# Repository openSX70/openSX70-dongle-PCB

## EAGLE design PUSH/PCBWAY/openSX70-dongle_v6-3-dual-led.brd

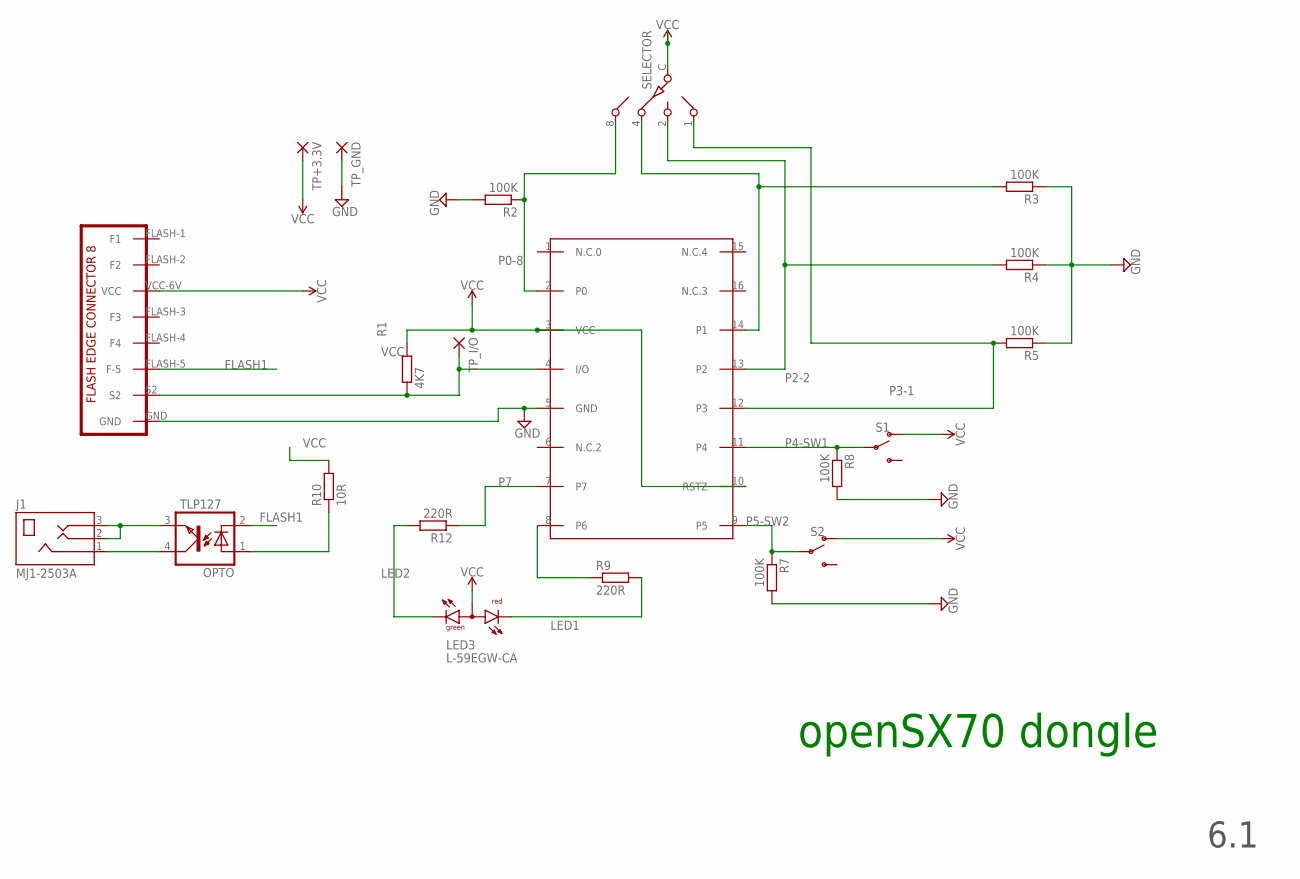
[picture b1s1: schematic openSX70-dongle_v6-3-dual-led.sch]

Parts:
DS2408: DS2408; SO16
J1: MJ1-2503A; CUI_MJ1-2503A
LED3: L-59EGW-CA
OPTO: TLP127; SO-4
R1: 4K7; R0603
R2, R3, R4, R5, R7, R8: 100K; R0603
R9, R12: 220R; R0603
R10: 10R; R0603
S1, S2: SWITCH-SPDT-SMD-RIGHT-ANGLE; SWITCH_SPST_SMD_A
SELECTOR: SW-C16
TP+3.3V: SMD2; SMD1,27-2,54
TP_GND: SMD2; SMD1,27-2,54
TP_I/O: SMD2; SMD1,27-2,54
U$2: SX70-FLASH-EDGE8-MALE-PROPER; SX70-FLASH-EDGE8

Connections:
FLASH1: OPTO.2 (C), U$2.FLASH-5 (F-5)
GND: DS2408.5 (GND), R2.2, R3.1, R4.1, R5.1, R7.2, R8.2, TP_GND.1, U$2.GND
LED1: LED3.1 (CR), R9.2
LED2: LED3.3 (CG), R12.2
unnamed: J1.1, OPTO.4 (COL)
unnamed: OPTO.1 (A), R10.1
unnamed: J1.2, J1.3, OPTO.3 (EMIT)
P0-8: DS2408.2 (P0), R2.1, SELECTOR.8
P1-4: DS2408.14 (P1), R3.2, SELECTOR.4
P2-2: DS2408.13 (P2), R4.2, SELECTOR.2
P3-1: DS2408.12 (P3), R5.2, SELECTOR.1
P4-SW1: DS2408.11 (P4), R8.1, S1.2
P5-SW2: DS2408.9 (P5), R7.1, S2.2
P6: DS2408.8 (P6), R9.1
P7: DS2408.7, R12.1
S2+: DS2408.4 (I/O), R1.1, TP_I/O.1, U$2.S2
VCC: DS2408.3 (VCC), DS2408.10 (RSTZ), LED3.2 (A), R1.2, R10.2, S1.1 (O), S2.1 (O), SELECTOR.C, TP+3.3V.1, U$2.VCC-6V (VCC)

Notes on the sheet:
openSX70 dongle
6.1

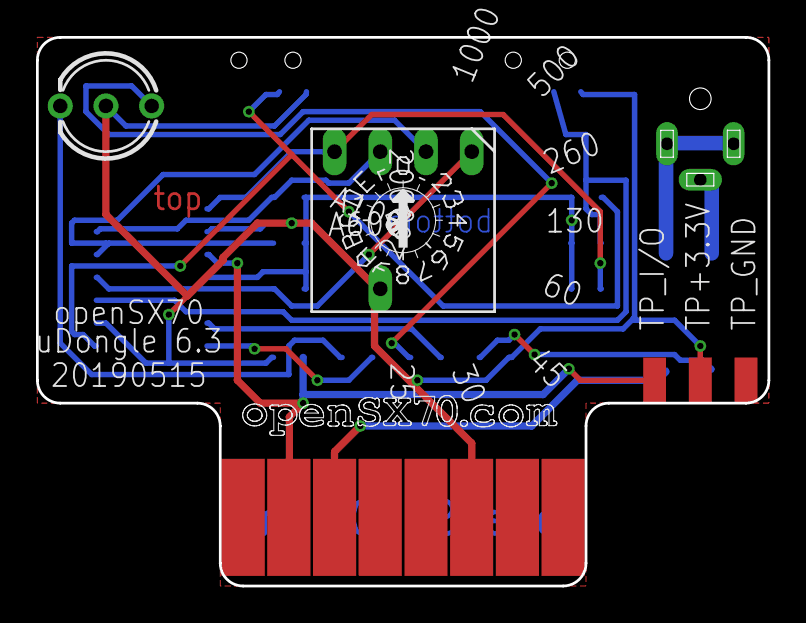
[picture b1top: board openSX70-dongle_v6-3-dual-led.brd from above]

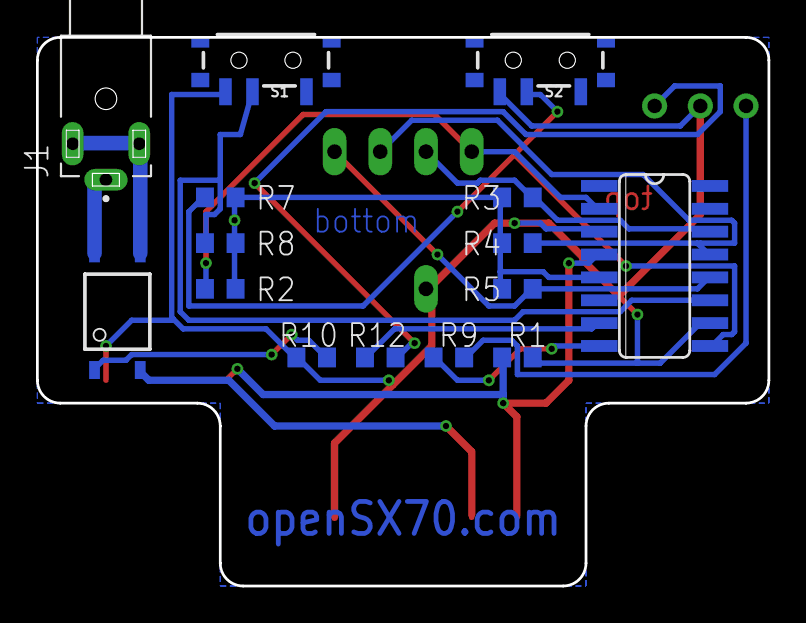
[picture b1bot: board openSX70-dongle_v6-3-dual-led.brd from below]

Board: 2 copper layers, 40.6 x 30.5 mm, 21 parts (15 on the bottom side), 17 nets.

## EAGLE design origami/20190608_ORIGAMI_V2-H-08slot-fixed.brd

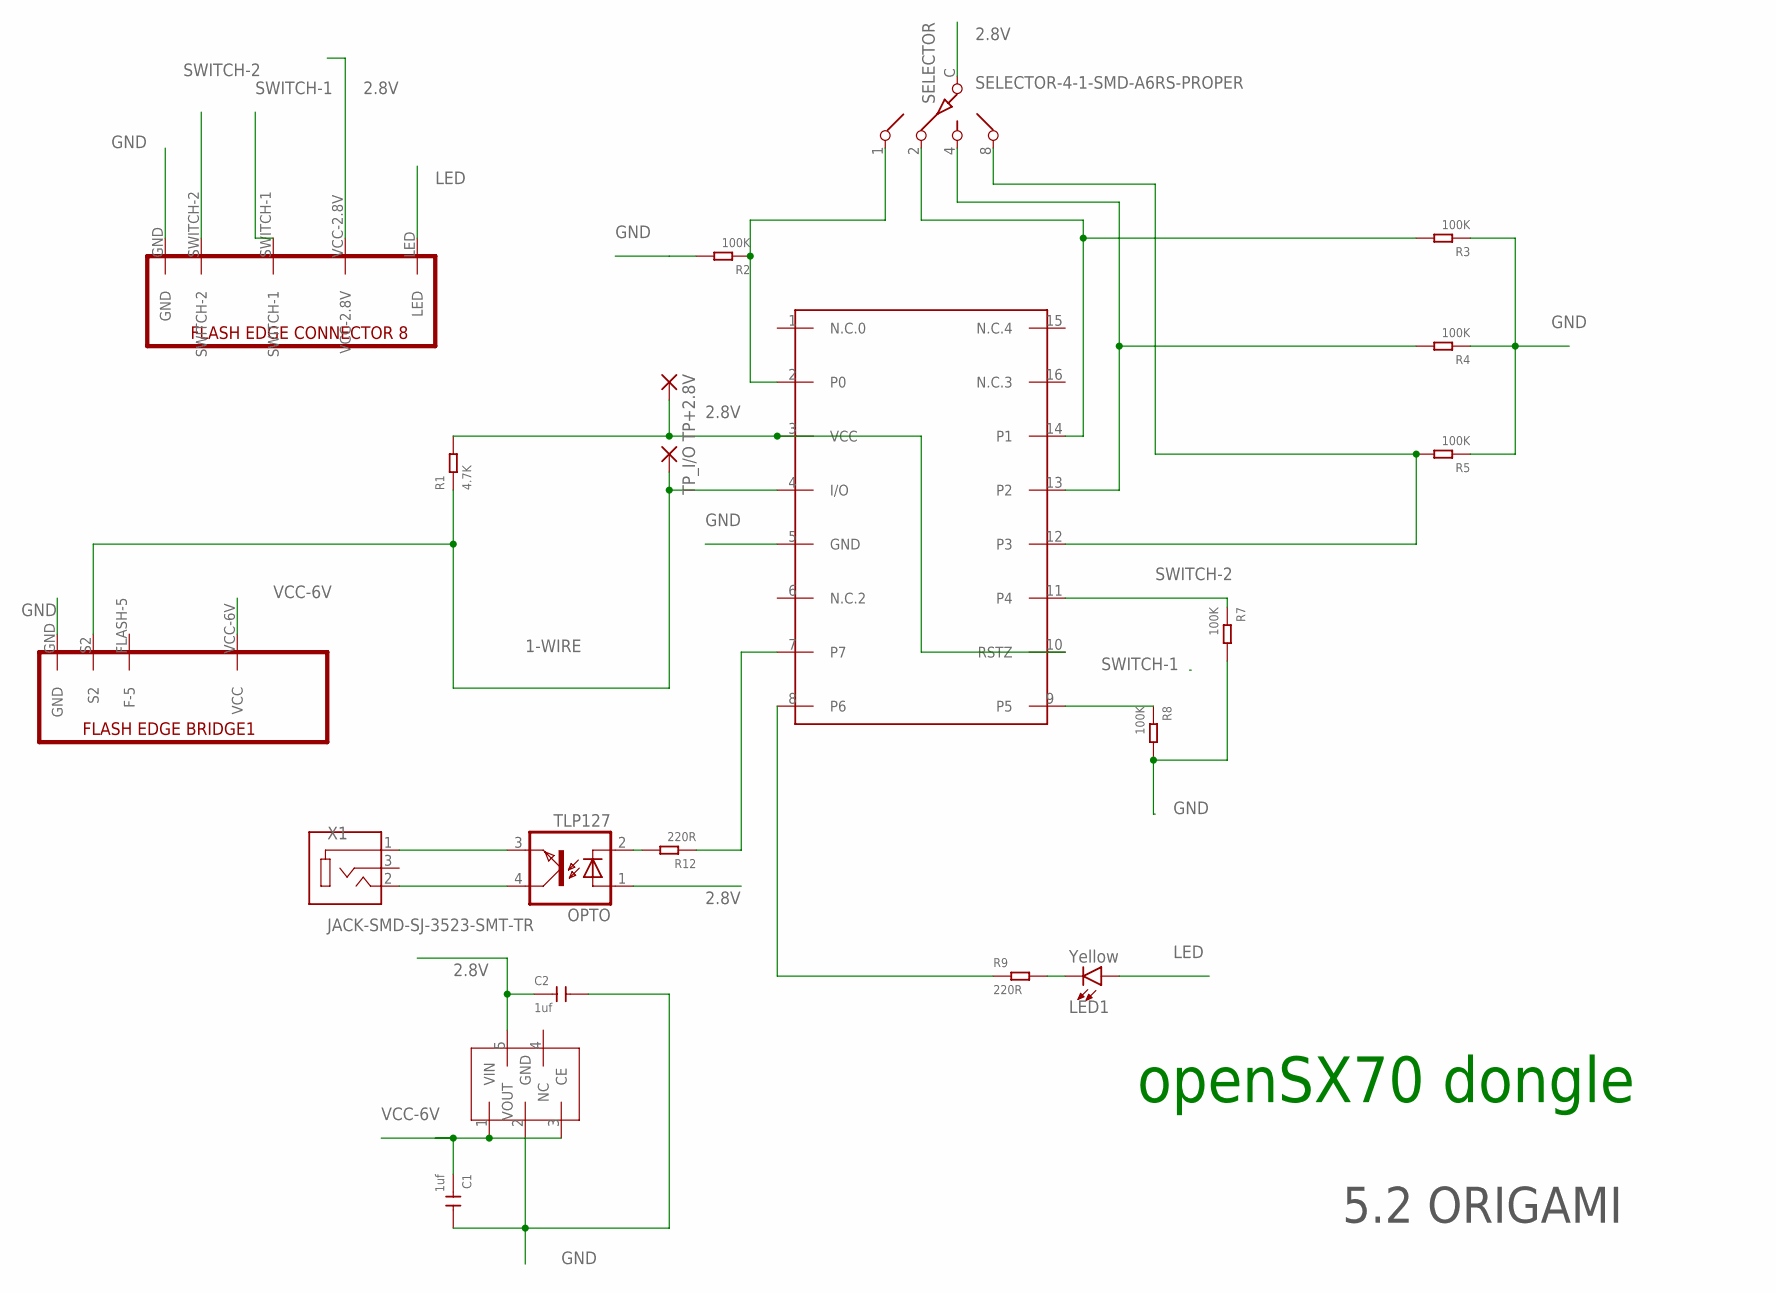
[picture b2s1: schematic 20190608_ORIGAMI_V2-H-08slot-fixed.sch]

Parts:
C1, C2: 1uf; C0603
DS2408: DS2408; SO16
LED1: Yellow; LED-1206
OPTO: TLP127; SO-4
R1: 4.7K; R0603
R2, R3, R4, R5, R7, R8: 100K; R0603
R9, R12: 220R; R0603
REG: NCP4688; SOT-23-5
SELECTOR: SELECTOR-4-1-SMD-A6RS-PROPER; A6RS-161RS
TP+2.8V: SMD2; SMD1,27-2,54
TP_I/O: SMD2; SMD1,27-2,54
U$1: FLASH-BRIDGE-SW1-SW2-LED; FLASH-8-BRIDGE-SW1-SW2-LED
U$2: FLASH-BRIDGE1; FLASH-8-BRIDGE1
X1: JACK-SMD-SJ-3523-SMT-TR; CUI_SJ-3523-SMT-TR

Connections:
1-WIRE: DS2408.4 (I/O), R1.1, TP_I/O.1, U$2.S2
2.8V: C2.1, DS2408.3 (VCC), DS2408.10 (RSTZ), OPTO.1 (A), R1.2, REG.5 (VOUT), SELECTOR.C, TP+2.8V.1, U$1.VCC-2.8V
GND: C1.2, C2.2, DS2408.5 (GND), R2.2, R3.1, R4.1, R5.1, R7.2, R8.2, REG.2 (GND), U$1.GND, U$2.GND
LED: LED1.A, U$1.LED
unnamed: OPTO.3 (EMIT), X1.1
unnamed: LED1.C, R9.2
unnamed: DS2408.2 (P0), R2.1, SELECTOR.1 (8)
unnamed: DS2408.14 (P1), R3.2, SELECTOR.2 (4)
unnamed: DS2408.13 (P2), R4.2, SELECTOR.4 (2)
unnamed: OPTO.4 (COL), X1.2
unnamed: DS2408.8 (P6), R9.1
unnamed: OPTO.2 (C), R12.2
unnamed: DS2408.7, R12.1
unnamed: DS2408.12 (P3), R5.2, SELECTOR.8 (1)
SWITCH-1: DS2408.9 (P5), R8.1, U$1.SWITCH-1
SWITCH-2: DS2408.11 (P4), R7.1, U$1.SWITCH-2
VCC-6V: C1.1, REG.1 (VIN), REG.3 (CE), U$2.VCC-6V (VCC)

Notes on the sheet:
openSX70 dongle
5.2 ORIGAMI

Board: 2 copper layers, 21 parts (0 on the bottom side), 17 nets, no tracks yet.

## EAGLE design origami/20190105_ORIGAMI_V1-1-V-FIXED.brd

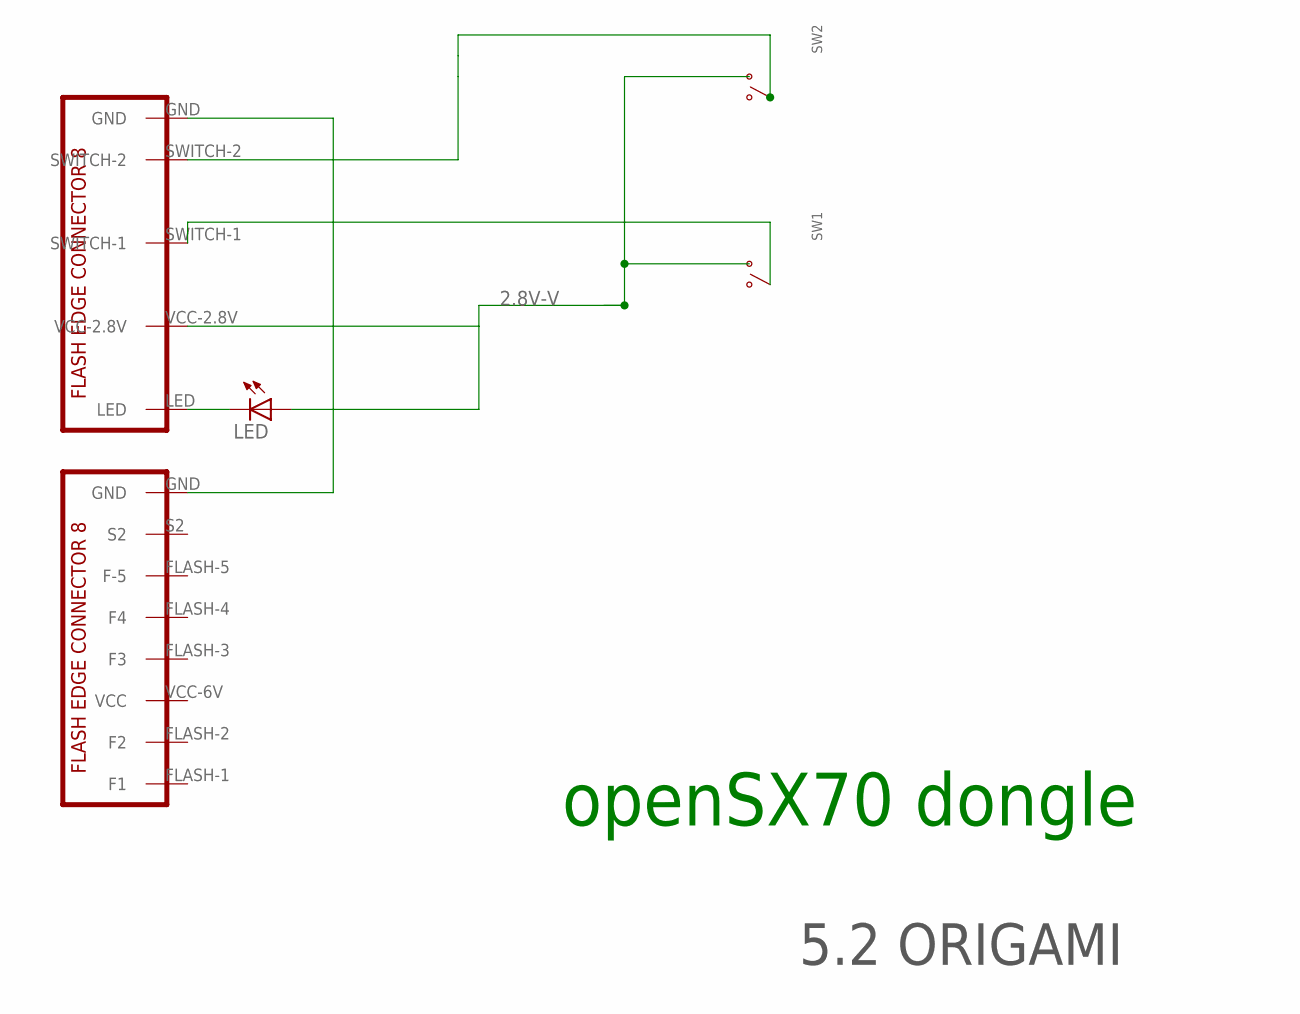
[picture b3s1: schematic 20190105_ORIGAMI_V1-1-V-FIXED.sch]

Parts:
LED: LEDCHIP-LED0805; CHIP-LED0805
SW1, SW2: MK-12C02 G1.5; SSSS810701
U$1: FLASH-BRIDGE-SW1-SW2-LED-SMALL; FLASH-8-BRIDGE-SW1-SW2-LED-SMALL
U$2: SX70-FLASH-EDGE8-MALE-LONG; SX70-FLASH-EDGE8-2

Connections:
2.8V-V: LED.A, SW1.1 (B), SW2.1 (B), U$1.VCC-2.8V
unnamed: U$1.GND, U$2.GND
unnamed: SW2.2 (COM), U$1.SWITCH-2
unnamed: LED.C, U$1.LED
unnamed: SW1.2 (COM), U$1.SWITCH-1

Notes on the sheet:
openSX70 dongle
5.2 ORIGAMI

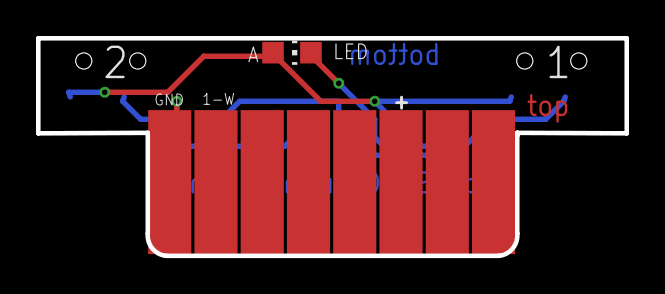
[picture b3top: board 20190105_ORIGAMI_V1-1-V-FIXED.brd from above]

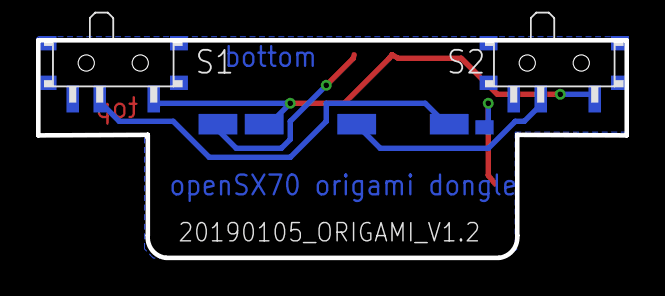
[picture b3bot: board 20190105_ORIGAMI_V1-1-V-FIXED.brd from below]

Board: 2 copper layers, 32.7 x 12.1 mm, 5 parts (3 on the bottom side), 5 nets.

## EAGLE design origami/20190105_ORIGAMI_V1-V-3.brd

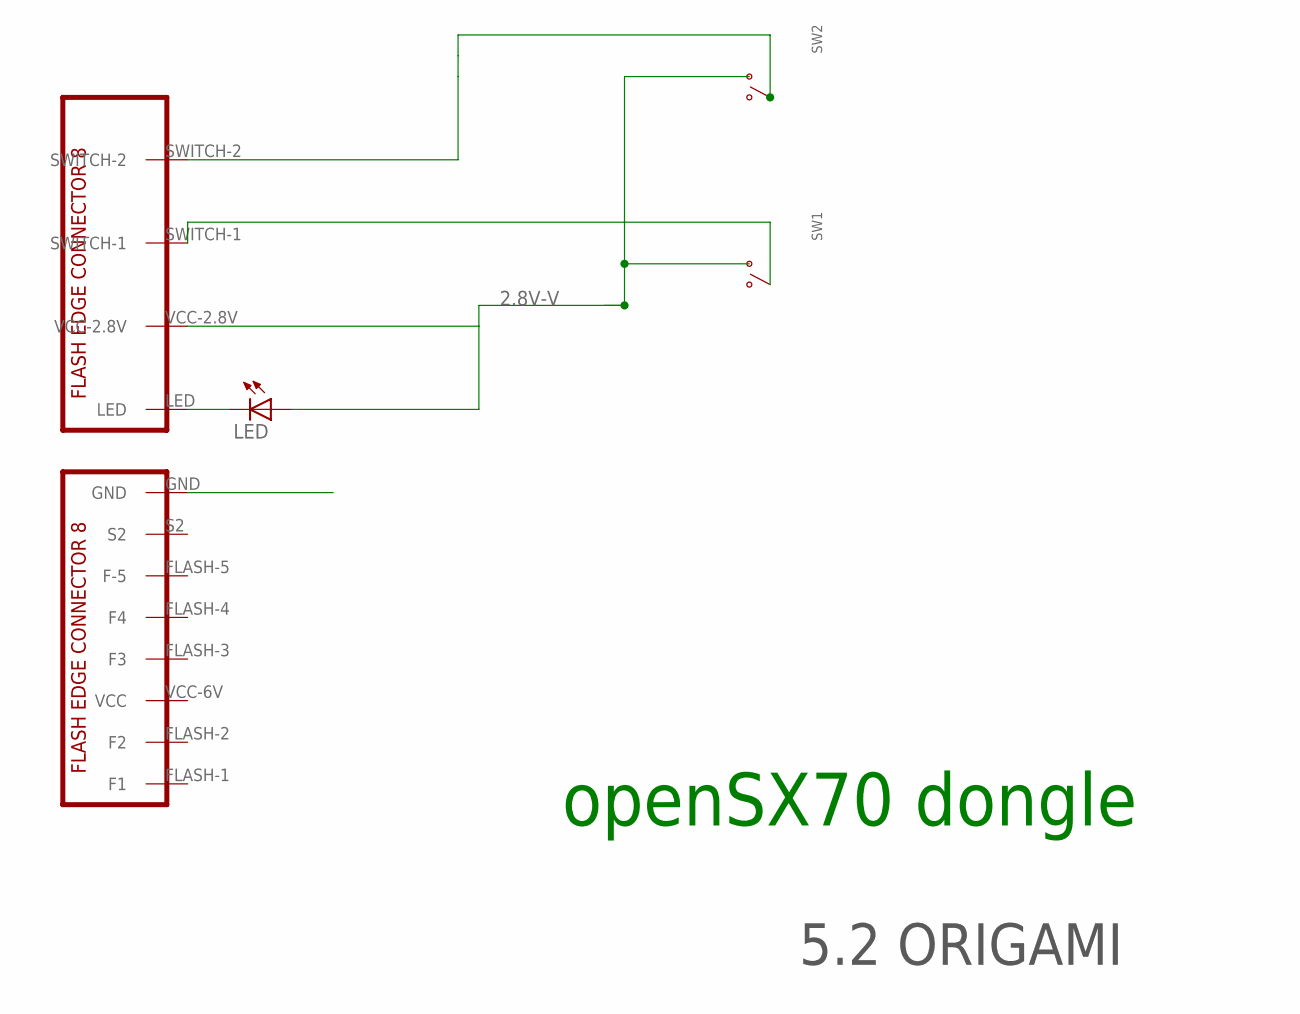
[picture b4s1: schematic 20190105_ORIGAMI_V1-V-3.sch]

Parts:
LED: LEDCHIP-LED0805; CHIP-LED0805
SW1, SW2: MK-12C02 G1.5; K3-1280S-SMALL
U$1: FLASH-BRIDGE-SW1-SW2-LED-SMALL-NO-GND; FLASH-8-BRIDGE-SW1-SW2-LED-SMALL-NO-GND
U$2: SX70-FLASH-EDGE8-MALE-LONG; SX70-FLASH-EDGE8-2

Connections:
2.8V-V: LED.A, SW1.P$3 (B), SW2.P$3 (B), U$1.VCC-2.8V
unnamed: SW2.P$2 (COM), U$1.SWITCH-2
unnamed: LED.C, U$1.LED
unnamed: SW1.P$2 (COM), U$1.SWITCH-1

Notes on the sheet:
openSX70 dongle
5.2 ORIGAMI

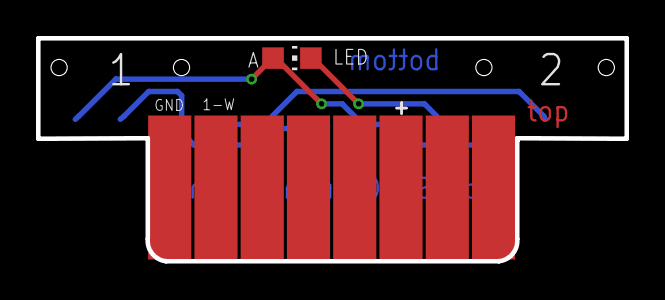
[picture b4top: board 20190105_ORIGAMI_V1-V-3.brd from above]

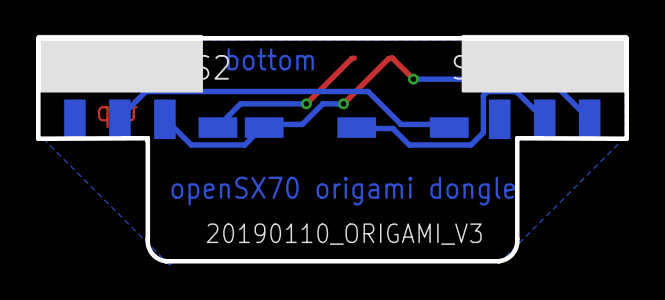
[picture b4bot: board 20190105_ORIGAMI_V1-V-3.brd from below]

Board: 2 copper layers, 32.7 x 12.4 mm, 5 parts (3 on the bottom side), 4 nets.

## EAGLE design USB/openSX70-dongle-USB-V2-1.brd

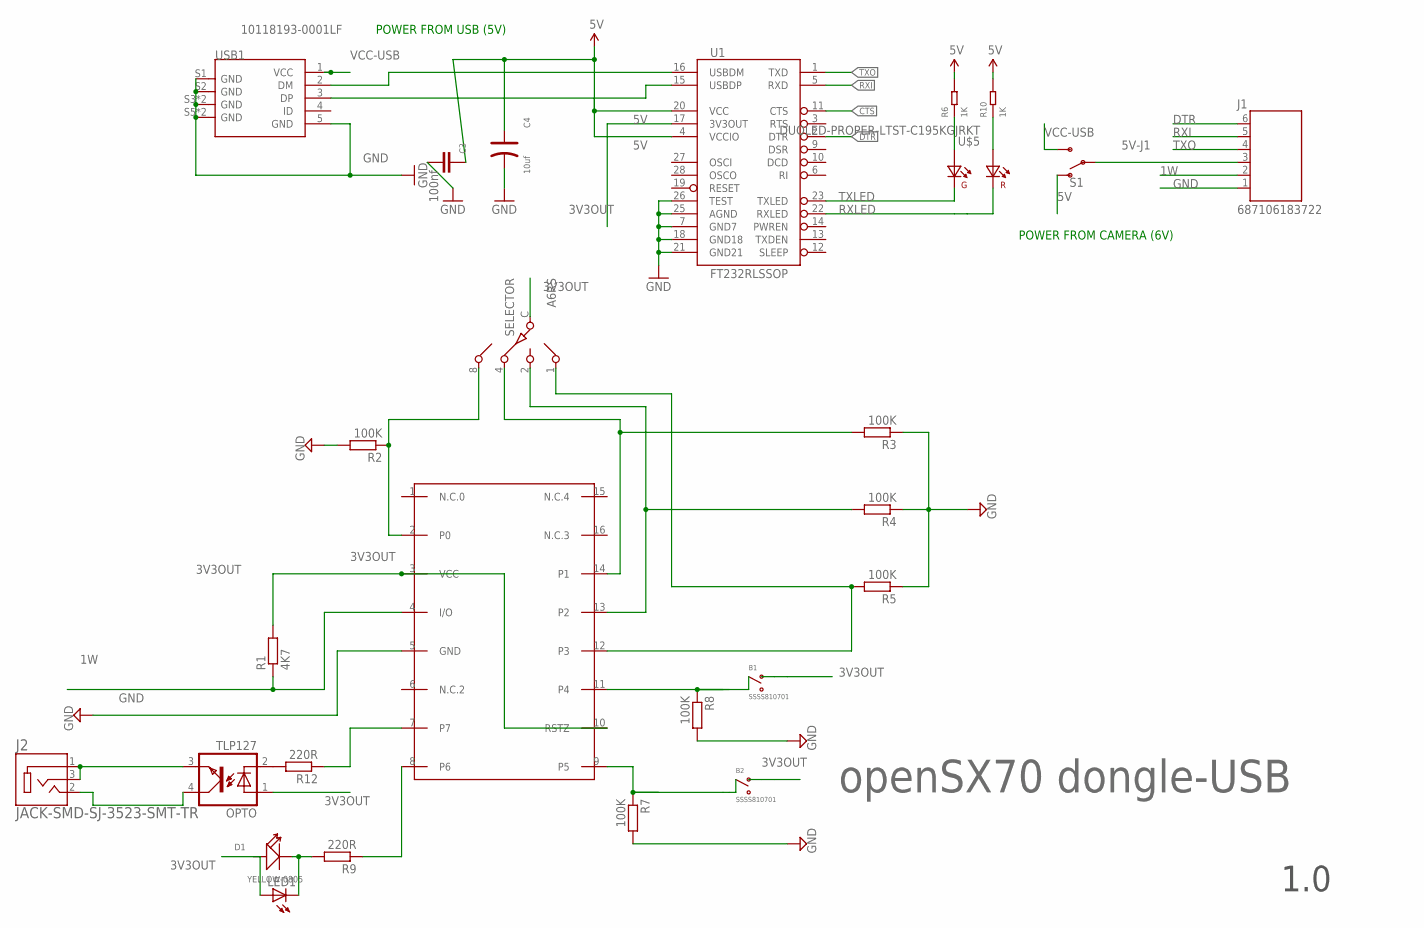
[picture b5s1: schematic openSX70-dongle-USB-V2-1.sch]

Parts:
B1, B2: SSSS810701
C3: 100nf; C0603
C4: 10uf; AVX-A
D1: YELLOW-0805; LED-0805
DS2408: DS2408; SO16
J1: 687106183722
J2: JACK-SMD-SJ-3523-SMT-TR; CUI_SJ-3523-SMT-TR
LED1: LED3MM
OPTO: TLP127; SO-4
R1: 4K7; R0603
R2, R3, R4, R5, R7, R8: 100K; R0603
R6, R10: 1K; R0603
R9, R12: 220R; R0603
S1: SWITCH-SPDT-SMD-RIGHT-ANGLE; SWITCH_SPST_SMD_A
SELECTOR: A6RS; A6RS-161RS
U1: FT232RLSSOP; SSOP28DB
U$5: DUOLED-PROPER-LTST-C195KGJRKT; LTST-BILED-15X16
USB1: 10118193-0001LF; MICRO-USB5+6P-SMD-0.65-B

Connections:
1W: DS2408.4 (I/O), J1.2 (5), R1.1
3V3OUT: B1.3 (A), B2.3 (A), D1.+, DS2408.3 (VCC), DS2408.10 (RSTZ), LED1.A, OPTO.1 (A), R1.2, SELECTOR.C, U1.17 (3V3OUT)
5V: C3.1, C4.+, R6.2, R10.2, S1.1 (O), U1.4 (VCCIO), U1.20 (VCC)
5V-J1: J1.3 (4), S1.2
CTS: U1.11 (CTS)
DTR: J1.6 (1), U1.2 (DTR)
GND: C3.2, C4.-, DS2408.5 (GND), J1.1 (6), R2.2, R3.1, R4.1, R5.1, R7.2, R8.2, U1.7 (GND7), U1.18 (GND18), U1.21 (GND21), U1.25 (AGND), U1.26 (TEST), USB1.5 (GND), USB1.S1 (GND), USB1.S2 (GND), USB1.S3 (GND), USB1.S4 (GND), USB1.S5 (GND), USB1.S6 (GND)
unnamed: J2.1, J2.3, OPTO.3 (EMIT)
unnamed: D1.-, LED1.K (C), R9.2
unnamed: DS2408.2 (P0), R2.1, SELECTOR.8
unnamed: DS2408.14 (P1), R3.2, SELECTOR.4
unnamed: DS2408.13 (P2), R4.2, SELECTOR.2
unnamed: B1.2 (COM), DS2408.11 (P4), R8.1
unnamed: B2.2 (COM), DS2408.9 (P5), R7.1
unnamed: DS2408.8 (P6), R9.1
unnamed: R10.1, U$5.P$2 (A2)
unnamed: OPTO.2 (C), R12.2
unnamed: DS2408.7, R12.1
unnamed: J2.2, OPTO.4 (COL)
unnamed: DS2408.12 (P3), R5.2, SELECTOR.1
unnamed: R6.1, U$5.P$1 (A1)
unnamed: U1.16 (USBDM), USB1.2 (DM)
RXI: J1.5 (2), U1.5 (RXD)
RXLED: U1.22 (RXLED), U$5.P$4 (K2)
TXLED: U1.23 (TXLED), U$5.P$3 (K1)
TXO: J1.4 (3), U1.1 (TXD)
USB_D+: U1.15 (USBDP), USB1.3 (DP)
VCC-USB: S1.3 (S), USB1.1 (VCC)

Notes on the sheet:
openSX70 dongle-USB
1.0
POWER FROM CAMERA (6V)
POWER FROM USB (5V)

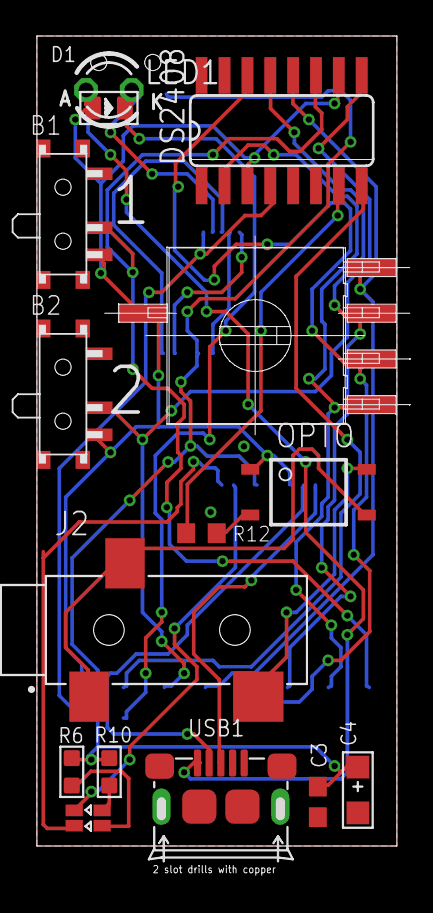
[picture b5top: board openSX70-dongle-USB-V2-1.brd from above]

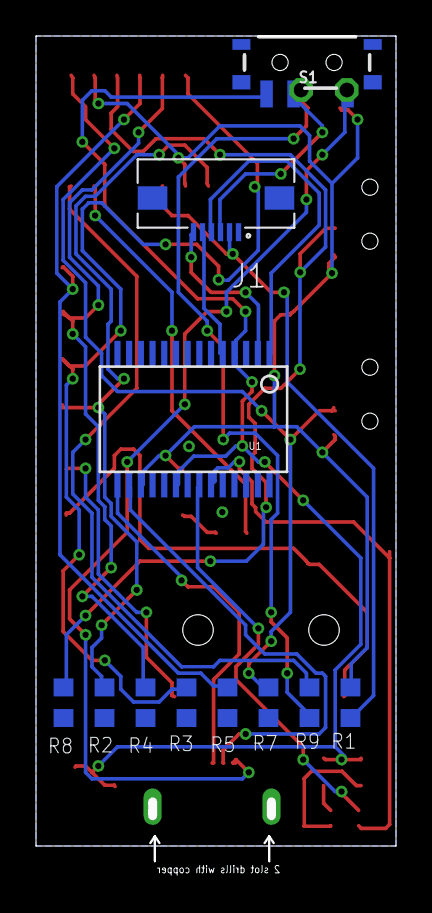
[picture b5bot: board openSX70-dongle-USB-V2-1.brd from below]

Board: 2 copper layers, 19.5 x 46.2 mm, 26 parts (11 on the bottom side), 27 nets.

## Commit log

2017-11-27 openSX70 initial commit of the dongle design
    openSX70 initial commit of the dongle design version 1.2
2017-11-27 added license
    https://creativecommons.org/licenses/by-nc/4.0/
2017-11-27 version 1.3
    Fixing stuff
2017-11-27 version 2.0 dongle
    EagleCAD version 2.0 dongle
2017-11-27 openSX70 dongle version 2.1
    Fixed stuff. Ordered from EasyEDA
2017-11-27 bad name. Fixing that.
2017-11-27 Proper upload of version 2.1 openSX70 dongle
    Version 2.1 manufactured by EasyEDA
2017-11-27 Gerber files
    Remember to choose .8mm board width.
2017-12-12 Moved to 2.2 there was a ground loose on the DS2408!!!
2017-12-22 Fix big flaws. Selector pin 8 was not connected to P3 (pin 12) D'ho!!
2017-12-23 P7 and P6 had a pulldown resistor when a pullup was needed. More D'ho! stuff.
2017-12-23 Changed version number on schematic.
2017-12-28 Had all the connections on the BCD wrong, now P0->pin2 DS->pin8 BCD P1->pin14 DS->pin4 BCD P2->pin13 DS->pin2 BCD P3->pin12 DS->pin1 BCD (same as in prototype). Also made the flash connector longer t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
2018-01-03 added www.openSX70.com in the bottom silkscreen
2018-01-03 Minor silkscreen changes
2018-01-03 added some labels and changed version number
2018-01-03 Cosmetic fixes after seeing the gerbers
2018-01-25 New version minor changes!
2018-01-26 no message
2018-01-26 Changed version number to 2.9 on schematic. Gerbars.
2018-01-27 Version 2.9 schematic
2018-01-27 Working on a new dongle!
2018-01-29 Added a 2.8V regulator needed to work with the 2.5V arduino. Removed R13 and R6 (pullup resistors to VCC for LED and opto), since they were not needed.
2018-01-31 Upload step 3D model
2018-02-01 trying to upload dongle 3D model
2018-02-02 new readme
2018-02-26 Working o a new "old" ugly dongle
2018-02-27 Getting ready to manufacture ugly dongles!
2018-03-05 New Gerbers, ready to order!
2018-04-21 towards manufacturing a dongle.
2018-04-21 New PCBA smaller uDongle
2018-04-24 Working towards a all SMD smaller uDongle2
2018-05-23 New 3.3 version: exactly as 3,2 but with round corners on connectors.
2018-07-06 Working on a new dongle with Jan
2018-07-18 new jan-hybrid work in progress
2018-07-24 NEW dimensions DXF
2018-07-24 new dongle WIP, new outline. testing if components fit
2018-10-01 dongle 3.6
2018-10-09 opened Eagle
2018-10-09 New layout for 90º BCD
2018-10-10 3.7 gerbers
2018-11-05 new usb'd board
2018-11-05 dongle questions
2018-12-05 new all in 1 USB dongle 20x45mm WIP
2018-12-17 new design, new parts
2018-12-17 20x45pcb
2018-12-17 USB dongle
2018-12-21 fixed dual led footprint
2019-01-03 new origami design
2019-01-04 new oriogami dongle
2019-01-04 WIP origami
2019-01-07 new origami and push(button) dongles test.
2019-01-07 chanmges
2019-01-07 3D parts
2019-01-08 MAJOR FOLDER ORGANIZATION
2019-01-08 sync
2019-01-09 fixed all and new switches
2019-01-09 new USB
2019-01-10 I am confused, hopefully this works
2019-01-10 new V3
2019-01-10 fixed holes in switch
2019-01-31 Minor fix
2019-02-08 minor changes
2019-07-12 new "final" uDongle
2019-07-15 NEW DUAL LED

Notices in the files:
parts and their libraries:
SparkFun-Switches: Licensing: Creative Commons ShareAlike 4.0 International - https://creativecommons.org/licenses/by-sa/4.0
